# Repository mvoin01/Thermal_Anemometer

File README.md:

# Thermal_Anemometer
Thermal_Anemometer ELEC70101

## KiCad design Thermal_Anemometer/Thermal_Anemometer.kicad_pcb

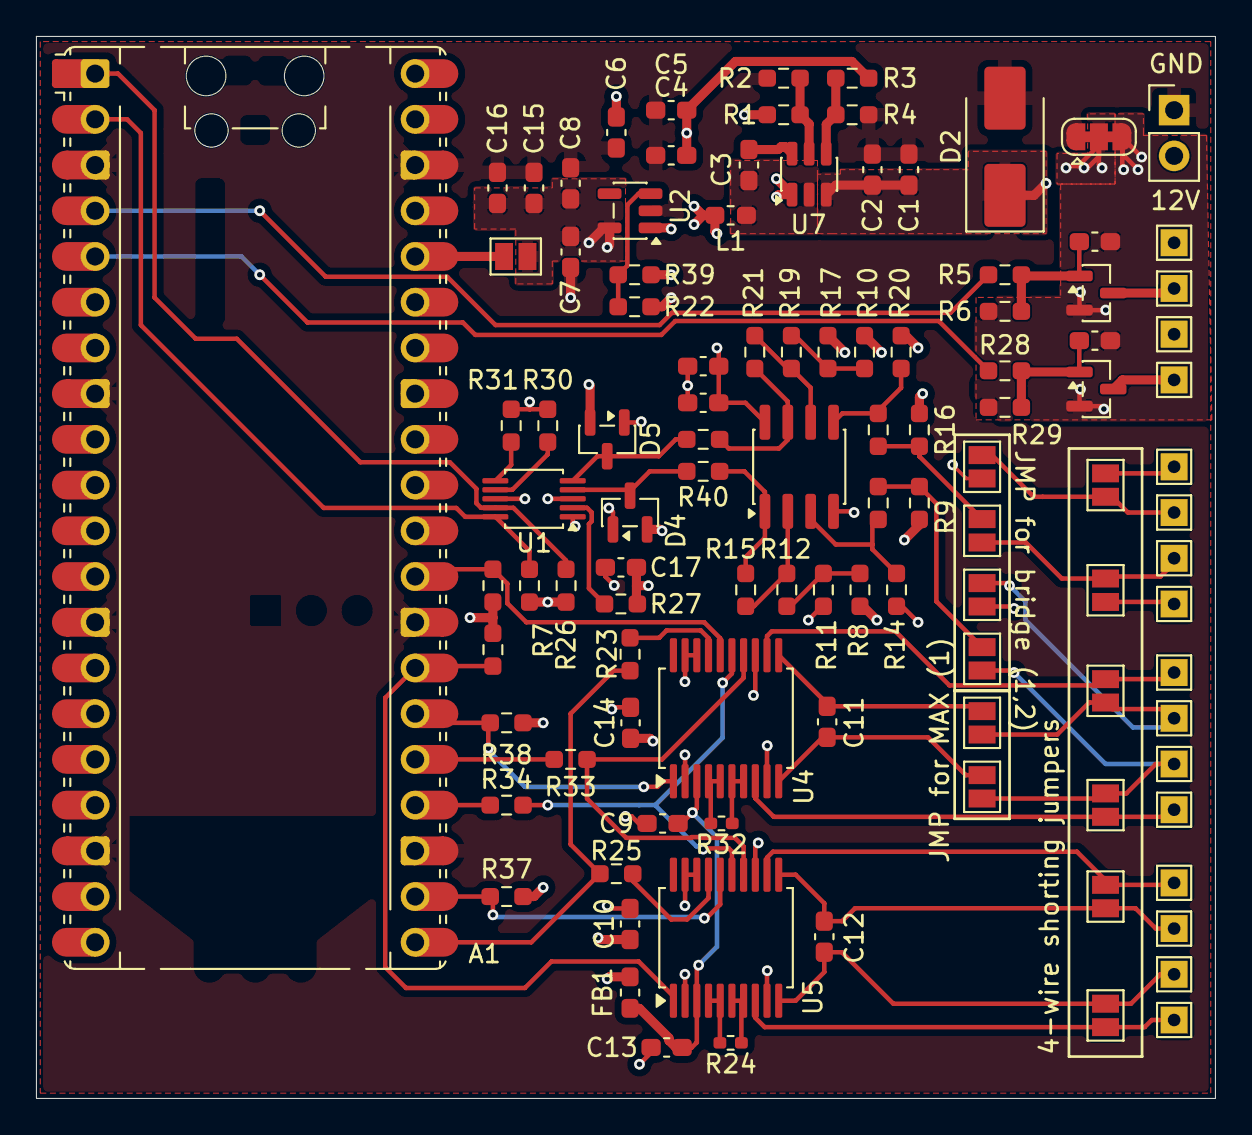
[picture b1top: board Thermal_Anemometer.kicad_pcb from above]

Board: 4 copper layers, 65.5 x 59.0 mm, 107 parts (0 on the bottom side), 63 nets.

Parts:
A1: RaspberryPi_Pico; RaspberryPi_Pico_Common_Unspecified
C1, C6, C15, C18: 10uF; C_0603_1608Metric_Pad1.08x0.95mm_HandSolder
C2, C3, C8, C9, C10, C13, C14, C16, C17, C19, C20, C21: 100nF; C_0603_1608Metric_Pad1.08x0.95mm_HandSolder
C4, C5, C7: 22uF; C_0603_1608Metric_Pad1.08x0.95mm_HandSolder
C11, C12: 10nF; C_0603_1608Metric_Pad1.08x0.95mm_HandSolder
D2: TVS 15V; D_SMB_Handsoldering
D4, D5: BAT54S; SOT-23
FB1: FerriteBead; L_0603_1608Metric_Pad1.05x0.95mm_HandSolder
J1, J2, J4, J5, J6, J7, J8, J9, J10, J11, J12, J13, J14, J15, J16, J17: Conn_01x01_Pin; TestPoint_THTPad_1.5x1.5mm_Drill0.7mm
J3: Conn_01x02_Pin; PinHeader_1x02_P2.54mm_Vertical
JP1, JP2, JP3, JP4, JP5, JP6, JP7, JP8, JP9, JP10, JP11, JP12, JP13: Jumper_2_Open; SolderJumper-2_P1.3mm_Open_Pad1.0x1.5mm
JP14: SolderJumper_3_Bridged123; SolderJumper-3_P1.3mm_Bridged123_RoundedPad1.0x1.5mm
L1: 33uH; L_0603_1608Metric_Pad1.05x0.95mm_HandSolder
Q3, Q4: DMN3404L; SOT-23
R1, R22: 33k; R_0603_1608Metric_Pad0.98x0.95mm_HandSolder
R2, R4, R7, R14, R15, R20, R21, R26, R27, R35, R36, R37, R38, R39: 10k; R_0603_1608Metric_Pad0.98x0.95mm_HandSolder
R3: 64.9k; R_0603_1608Metric_Pad0.98x0.95mm_HandSolder
R5, R28: 100; R_0603_1608Metric_Pad0.98x0.95mm_HandSolder
R6, R29, R30, R31: 100k; R_0603_1608Metric_Pad0.98x0.95mm_HandSolder
R8, R9, R10, R11, R12, R13, R16, R17, R18, R19: 1k; R_0603_1608Metric_Pad0.98x0.95mm_HandSolder
R23, R25, R33, R34: 22; R_0603_1608Metric_Pad0.98x0.95mm_HandSolder
R24, R32: 2.2k; R_0402_1005Metric_Pad0.72x0.64mm_HandSolder
R40, R41: 180; R_0603_1608Metric_Pad0.98x0.95mm_HandSolder
U1: ADS1115IDGS; TSSOP-10_3x3mm_P0.5mm
U2: AP2112K-3.3; SOT-23-5
U4, U5: MAX31865xAP; SSOP-20_5.3x7.2mm_P0.65mm
U6: LM358; SOIC-8_3.9x4.9mm_P1.27mm
U7: AP62300WU; TSOT-23-6

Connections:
+3.3V: C7.1, C8.1, C10.1, C14.1, C15.1, C16.1, C17.1, D4.2 (K), D5.2 (K), FB1.1, JP1.2 (B), R7.1, R8.1, R9.1, R10.1, R16.1, R26.1, R27.1, R35.1, R36.1, R37.1, R38.1, U1.8 (VDD), U2.5 (VOUT), U4.2 (DVDD), U5.2 (DVDD)
+3.3VA: C9.1, C13.1, FB1.2, U4.3 (VDD), U5.3 (VDD)
+6V: C4.1, C5.1, C6.1, C18.1, C19.1, J11.1 (Pin_1_1), J13.1 (Pin_1_1), L1.2, R3.1, R39.1, U2.1 (VIN), U6.8 (V+)
+12V: C1.1, C2.1, D2.1 (K), J3.2, R1.1, U7.3 (IN)
/ADC/ADC_RDY/ALERT: R27.2, U1.2 (ALERT/RDY)
/ADC/I2C_SCL: A1.2 (GPIO1), R7.2, U1.10 (SCL)
/ADC/I2C_SDA: A1.1 (GPIO0), R26.2, U1.9 (SDA)
/A_OUT1: D4.3 (COM), R40.2, U1.4 (AIN0)
/A_OUT2: D5.3 (COM), R41.2, U1.5 (AIN1)
/MAX31865/REFIN1+: R32.2, U4.4 (BIAS), U4.5 (REFIN+)
/MAX31865/REFIN1-: R32.1, U4.6 (REFIN-), U4.7 (ISENSOR)
/MAX31865/REFIN3+: R24.2, U5.4 (BIAS), U5.5 (REFIN+)
/MAX31865/REFIN3-: R24.1, U5.6 (REFIN-), U5.7 (ISENSOR)
/PT1000_1+: C11.1, J10.1 (Pin_1_1), JP3.2 (B), JP6.2 (B), JP10.1 (A), JP10.2 (B), U4.10 (RTDIN+)
/PT1000_1-: C11.2, J9.1 (Pin_1_1), JP2.2 (B), JP7.2 (B), JP11.1 (A), JP11.2 (B), U4.11 (RTDIN-)
/PT1000_2+: J2.1 (Pin_1_1), JP4.2 (B), JP8.2 (B)
/PT1000_2-: J4.1 (Pin_1_1), JP5.2 (B), JP9.2 (B)
/PT1000_3+: C12.1, J15.1 (Pin_1_1), JP12.2 (B), U5.10 (RTDIN+)
/PT1000_3-: C12.2, J16.1 (Pin_1_1), JP13.2 (B), U5.11 (RTDIN-)
/PT1000_4Wire_1+: J7.1 (Pin_1_1), JP3.1 (A), U4.8 (FORCE+)
/PT1000_4Wire_1-: J8.1 (Pin_1_1), JP2.1 (A), U4.12 (FORCE-)
/PT1000_4Wire_2+: J1.1 (Pin_1_1), JP4.1 (A)
/PT1000_4Wire_2-: J5.1 (Pin_1_1), JP5.1 (A)
/PT1000_4Wire_3+: J14.1 (Pin_1_1), JP12.1 (A), U5.8 (FORCE+)
/PT1000_4Wire_3-: J17.1 (Pin_1_1), JP13.1 (A), U5.12 (FORCE-)
/RP_Pico/3V3_Pico: A1.36 (3V3), JP1.1 (A)
/SPI_CLK: R34.2, U4.15 (SCLK), U5.15 (SCLK)
/SPI_MISO: A1.21 (GPIO16), R23.2, R25.2
/SPI_MOSI: R33.2, U4.14 (SDI), U5.14 (SDI)
/SPI_nDRDY1: A1.26 (GPIO20), R38.2, U4.1 (~DRDY)
/SPI_nDRDY2: A1.27 (GPIO21), R36.2, U5.1 (~DRDY)
/Wheatstone_Bridge/PT1000_1+W: JP6.1 (A), R9.2, R13.1
/Wheatstone_Bridge/PT1000_2+W: JP8.1 (A), R16.2, R18.1
/nCS1: A1.29 (GPIO22), R35.2, U4.16 (~CS)
/nCS2: A1.22 (GPIO17), R37.2, U5.16 (~CS)
/uHeater1-: J12.1 (Pin_1_1), Q4.3 (D)
/uHeater1_EN: A1.4 (GPIO2), R5.1
/uHeater2-: J6.1 (Pin_1_1), Q3.3 (D)
/uHeater2_EN: A1.5 (GPIO3), R28.1
GND: A1.3 (GND), A1.8 (GND), A1.13 (GND), A1.18 (GND), A1.23 (GND), A1.28 (GND), A1.38 (GND), C1.2, C2.2, C4.2, C5.2, C6.2, C7.2, C8.2, C15.2, C16.2, C17.2, D2.2 (A), J3.1, JP14.1 (A), R2.2, R4.2, R22.2, U2.2 (GND), U7.1 (GND)
GNDA: C9.2, C10.2, C13.2, C14.2, C18.2, C19.2, D4.1 (A), D5.1 (A), JP7.1 (A), JP9.1 (A), JP14.2 (C), R11.2, R14.2, R17.2, R20.2, R30.2, R31.2, U1.1 (ADDR), U1.3 (GND), U4.9 (FORCE2), U4.13 (GND), U4.18 (DGND), U4.19 (GND), U5.9 (FORCE2), U5.13 (GND), U5.18 (DGND), U5.19 (GND), U6.4 (V-)
GNDPWR: C20.2, C21.2, JP14.3 (B), Q3.2 (S), Q4.2 (S), R6.2, R29.2
unnamed: A1.24 (GPIO18), R34.1
unnamed: A1.25 (GPIO19), R33.1
unnamed: C21.1, Q3.1 (G), R28.2, R29.1
unnamed: C20.1, Q4.1 (G), R5.2, R6.1
unnamed: R10.2, R17.1, R19.1
unnamed: R8.2, R11.1, R12.1
unnamed: R15.2, R40.1, U6.1
unnamed: R21.2, R41.1, U6.7
unnamed: R31.1, U1.6 (AIN2)
unnamed: R30.1, U1.7 (AIN3)
unnamed: R22.1, R39.2, U2.3 (EN)
unnamed: R23.1, U4.17 (SDO)
unnamed: R25.1, U5.17 (SDO)
unnamed: R13.2, R14.1, U6.3 (+)
unnamed: R12.2, R15.1, U6.2 (-)
unnamed: R18.2, R20.1, U6.5 (+)
unnamed: R19.2, R21.1, U6.6 (-)
unnamed: C3.1, U7.6 (BST)
unnamed: R1.2, R2.1, U7.5 (EN)
unnamed: R3.2, R4.1, U7.4 (FB)
unnamed: C3.2, L1.1, U7.2 (SW)
